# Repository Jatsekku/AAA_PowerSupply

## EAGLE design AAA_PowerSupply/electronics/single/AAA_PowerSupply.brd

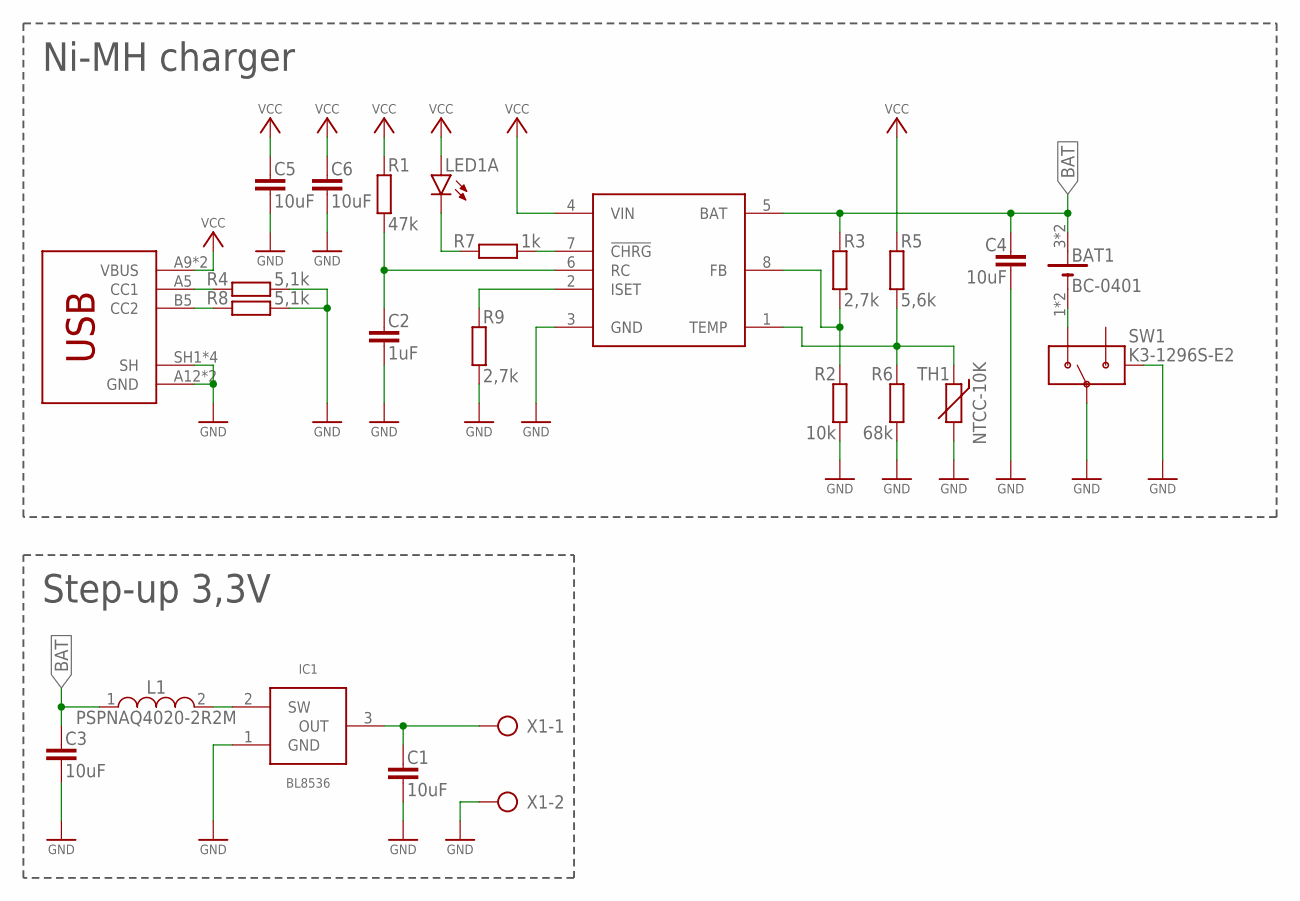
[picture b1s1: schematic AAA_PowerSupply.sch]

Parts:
BAT1: BC-0401
C1, C3, C4, C5, C6: 10uF; C0805
C2: 1uF; C0805
IC1: BL8536; SOT23
IC2: CN3085; SOP8_THERMAL
L1: PSPNAQ4020-2R2M; L-4X4
LED1: LSG-T676; WL-SFCW-0603
R1: 47k; R0805
R2: 10k; R0805
R3, R9: 2,7k; R0805
R4, R8: 5,1k; R0805
R5: 5,6k; R0805
R6: 68k; R0805
R7: 1k; R0805
SW1: K3-1296S-E2
TH1: NTCC-10K; RS-2,5
X1: AK500/2
X2: HC-TYPE-C-6P-01QT

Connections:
BAT: BAT1.3 (+), BAT1.4 (+), C3.1, C4.1, IC2.5 (BAT), L1.1, R3.1
GND: C1.2, C2.2, C3.2, C4.2, C5.2, C6.2, IC1.1 (GND), IC2.3 (GND), R2.2, R4.2, R6.2, R8.2, R9.1, SW1.P, SW1.SH1 (SH), SW1.SH2 (SH), SW1.SH3 (SH), SW1.SH4 (SH), TH1.2, X1.2, X2.A12 (GND), X2.B12 (GND), X2.SH1 (SH), X2.SH2 (SH), X2.SH3 (SH), X2.SH4 (SH)
unnamed: IC2.7 (!CHRG), R7.2
unnamed: LED1.P$1 (C), R7.1
unnamed: C2.1, IC2.6 (RC), R1.2
unnamed: IC2.2 (ISET), R9.2
unnamed: C1.1, IC1.3 (OUT), X1.1
unnamed: IC1.2 (SW), L1.2
unnamed: IC2.8 (FB), R2.1, R3.2
unnamed: IC2.1 (TEMP), R5.2, R6.1, TH1.1
unnamed: BAT1.1 (-), BAT1.2 (-), SW1.O
unnamed: R4.1, X2.A5 (CC1)
unnamed: R8.1, X2.B5 (CC2)
VCC: C5.1, C6.1, IC2.4 (VIN), LED1.P$2 (A), R1.1, R5.1, X2.A9 (VBUS), X2.B9 (VBUS)

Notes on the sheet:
Ni-MH charger
Step-up 3,3V

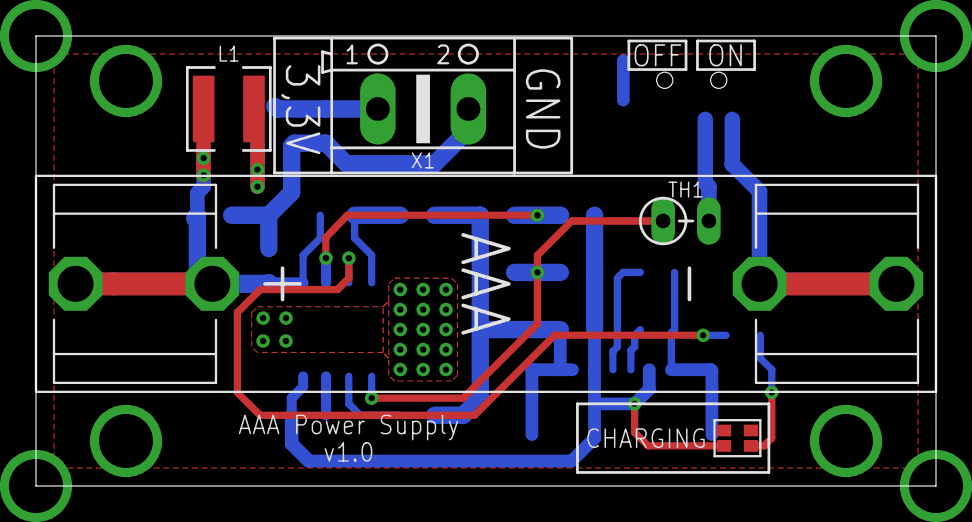
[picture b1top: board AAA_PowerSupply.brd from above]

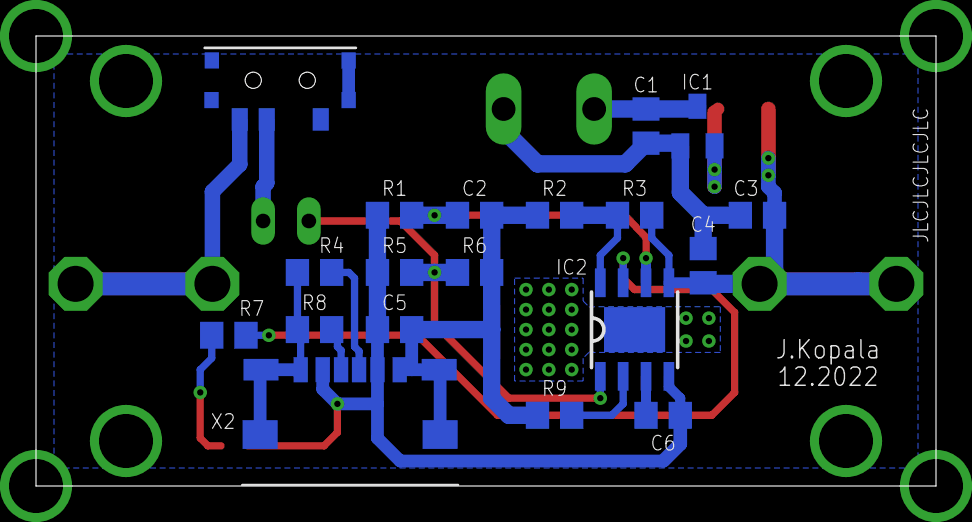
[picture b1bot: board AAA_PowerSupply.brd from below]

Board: 2 copper layers, 50.0 x 25.0 mm, 24 parts (19 on the bottom side), 14 nets.

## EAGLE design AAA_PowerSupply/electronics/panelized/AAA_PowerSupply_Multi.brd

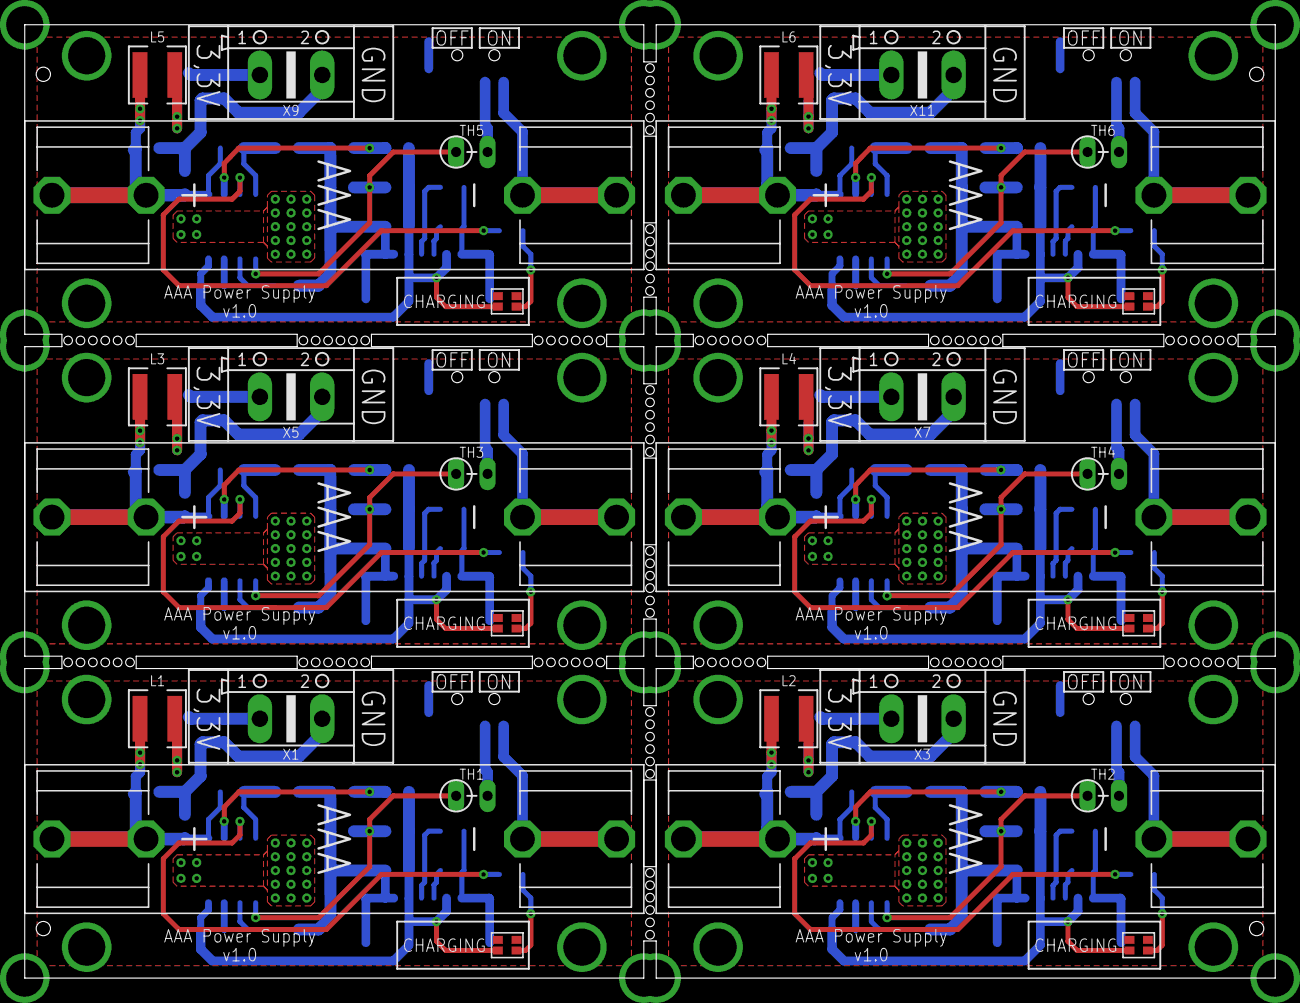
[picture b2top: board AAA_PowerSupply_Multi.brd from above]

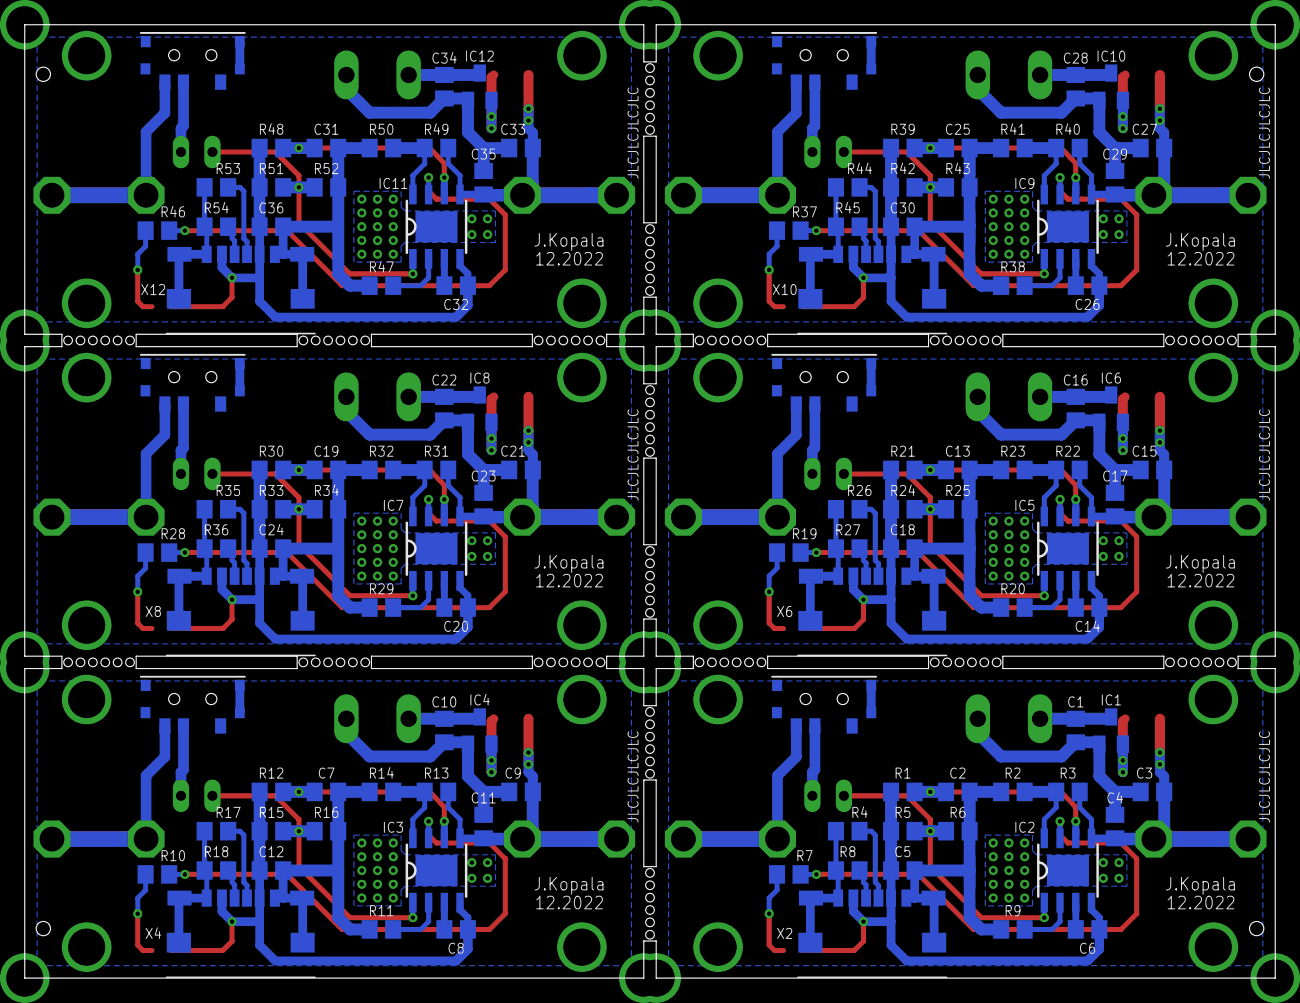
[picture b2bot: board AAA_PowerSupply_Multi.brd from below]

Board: 2 copper layers, 101.0 x 77.0 mm, 144 parts (114 on the bottom side), 84 nets.

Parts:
BAT1, BAT2, BAT3, BAT4, BAT5, BAT6: BC-0401
C1, C3, C4, C5, C6, C8, C9, C10, C11, C12, C14, C15, C16, C17, C18, C20, C21, C22, C23, C24, C26, C27, C28, C29, C30, C32, C33, C34, C35, C36: 10uF; C0805
C2, C7, C13, C19, C25, C31: 1uF; C0805
IC1, IC4, IC6, IC8, IC10, IC12: BL8536; SOT23
IC2, IC3, IC5, IC7, IC9, IC11: CN3085; SOP8_THERMAL
L1, L2, L3, L4, L5, L6: PSPNAQ4020-2R2M; L-4X4
LED1, LED2, LED3, LED4, LED5, LED6: LSG-T676; WL-SFCW-0603
R1, R12, R21, R30, R39, R48: 47k; R0805
R2, R14, R23, R32, R41, R50: 10k; R0805
R3, R9, R11, R13, R20, R22, R29, R31, R38, R40, R47, R49: 2,7k; R0805
R4, R8, R17, R18, R26, R27, R35, R36, R44, R45, R53, R54: 5,1k; R0805
R5, R15, R24, R33, R42, R51: 5,6k; R0805
R6, R16, R25, R34, R43, R52: 68k; R0805
R7, R10, R19, R28, R37, R46: 1k; R0805
SW1, SW2, SW3, SW4, SW5, SW6: K3-1296S-E2
TH1, TH2, TH3, TH4, TH5, TH6: NTCC-10K; RS-2,5
X1, X3, X5, X7, X9, X11: AK500/2
X2, X4, X6, X8, X10, X12: HC-TYPE-C-6P-01QT

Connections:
BAT: BAT1.3, BAT1.4, C3.1, C4.1, IC2.5, L1.1, R3.1
BAT1: BAT2.3, BAT2.4, C9.1, C11.1, IC3.5, L2.1, R13.1
BAT2: BAT3.3, BAT3.4, C15.1, C17.1, IC5.5, L3.1, R22.1
BAT3: BAT4.3, BAT4.4, C21.1, C23.1, IC7.5, L4.1, R31.1
BAT4: BAT5.3, BAT5.4, C27.1, C29.1, IC9.5, L5.1, R40.1
BAT5: BAT6.3, BAT6.4, C33.1, C35.1, IC11.5, L6.1, R49.1
GND: C1.2, C2.2, C3.2, C4.2, C5.2, C6.2, IC1.1, IC2.3, R2.2, R4.2, R6.2, R8.2, R9.1, SW1.P, SW1.SH1, SW1.SH2, SW1.SH3, SW1.SH4, TH1.2, X1.2, X2.A12, X2.B12, X2.SH1, X2.SH2, X2.SH3, X2.SH4
GND1: C7.2, C8.2, C9.2, C10.2, C11.2, C12.2, IC3.3, IC4.1, R11.1, R14.2, R16.2, R17.2, R18.2, SW2.P, SW2.SH1, SW2.SH2, SW2.SH3, SW2.SH4, TH2.2, X3.2, X4.A12, X4.B12, X4.SH1, X4.SH2, X4.SH3, X4.SH4
GND2: C13.2, C14.2, C15.2, C16.2, C17.2, C18.2, IC5.3, IC6.1, R20.1, R23.2, R25.2, R26.2, R27.2, SW3.P, SW3.SH1, SW3.SH2, SW3.SH3, SW3.SH4, TH3.2, X5.2, X6.A12, X6.B12, X6.SH1, X6.SH2, X6.SH3, X6.SH4
GND3: C19.2, C20.2, C21.2, C22.2, C23.2, C24.2, IC7.3, IC8.1, R29.1, R32.2, R34.2, R35.2, R36.2, SW4.P, SW4.SH1, SW4.SH2, SW4.SH3, SW4.SH4, TH4.2, X7.2, X8.A12, X8.B12, X8.SH1, X8.SH2, X8.SH3, X8.SH4
GND4: C25.2, C26.2, C27.2, C28.2, C29.2, C30.2, IC9.3, IC10.1, R38.1, R41.2, R43.2, R44.2, R45.2, SW5.P, SW5.SH1, SW5.SH2, SW5.SH3, SW5.SH4, TH5.2, X9.2, X10.A12, X10.B12, X10.SH1, X10.SH2, X10.SH3, X10.SH4
GND5: C31.2, C32.2, C33.2, C34.2, C35.2, C36.2, IC11.3, IC12.1, R47.1, R50.2, R52.2, R53.2, R54.2, SW6.P, SW6.SH1, SW6.SH2, SW6.SH3, SW6.SH4, TH6.2, X11.2, X12.A12, X12.B12, X12.SH1, X12.SH2, X12.SH3, X12.SH4
unnamed: C7.1, IC3.6, R12.2
unnamed: IC2.7, R7.2
unnamed: LED1.P$1, R7.1
unnamed: C2.1, IC2.6, R1.2
unnamed: IC2.2, R9.2
unnamed: C1.1, IC1.3, X1.1
unnamed: IC3.2, R11.2
unnamed: IC1.2, L1.2
unnamed: IC2.8, R2.1, R3.2
unnamed: C10.1, IC4.3, X3.1
unnamed: IC4.2, L2.2
unnamed: IC2.1, R5.2, R6.1, TH1.1
unnamed: IC3.8, R13.2, R14.1
unnamed: IC3.1, R15.2, R16.1, TH2.1
unnamed: IC3.7, R10.2
unnamed: LED2.P$1, R10.1
unnamed: BAT1.1, BAT1.2, SW1.O
unnamed: R4.1, X2.A5
unnamed: R8.1, X2.B5
unnamed: BAT2.1, BAT2.2, SW2.O
unnamed: R17.1, X4.A5
unnamed: R18.1, X4.B5
unnamed: C13.1, IC5.6, R21.2
unnamed: IC5.2, R20.2
unnamed: C16.1, IC6.3, X5.1
unnamed: IC6.2, L3.2
unnamed: IC5.8, R22.2, R23.1
unnamed: IC5.1, R24.2, R25.1, TH3.1
unnamed: IC5.7, R19.2
unnamed: LED3.P$1, R19.1
unnamed: BAT3.1, BAT3.2, SW3.O
unnamed: R26.1, X6.A5
unnamed: R27.1, X6.B5
unnamed: C19.1, IC7.6, R30.2
unnamed: IC7.2, R29.2
unnamed: C22.1, IC8.3, X7.1
unnamed: IC8.2, L4.2
unnamed: IC7.8, R31.2, R32.1
unnamed: IC7.1, R33.2, R34.1, TH4.1
unnamed: IC7.7, R28.2
unnamed: LED4.P$1, R28.1
unnamed: BAT4.1, BAT4.2, SW4.O
unnamed: R35.1, X8.A5
unnamed: R36.1, X8.B5
unnamed: C25.1, IC9.6, R39.2
unnamed: IC9.2, R38.2
unnamed: C28.1, IC10.3, X9.1
unnamed: IC10.2, L5.2
unnamed: IC9.8, R40.2, R41.1
unnamed: IC9.1, R42.2, R43.1, TH5.1
unnamed: IC9.7, R37.2
unnamed: LED5.P$1, R37.1
unnamed: BAT5.1, BAT5.2, SW5.O
unnamed: R44.1, X10.A5
unnamed: R45.1, X10.B5
unnamed: C31.1, IC11.6, R48.2
unnamed: IC11.2, R47.2
unnamed: C34.1, IC12.3, X11.1
unnamed: IC12.2, L6.2
unnamed: IC11.8, R49.2, R50.1
unnamed: IC11.1, R51.2, R52.1, TH6.1
unnamed: IC11.7, R46.2
unnamed: LED6.P$1, R46.1
unnamed: BAT6.1, BAT6.2, SW6.O
unnamed: R53.1, X12.A5
unnamed: R54.1, X12.B5
VCC: C5.1, C6.1, IC2.4, LED1.P$2, R1.1, R5.1, X2.A9, X2.B9
VCC1: C8.1, C12.1, IC3.4, LED2.P$2, R12.1, R15.1, X4.A9, X4.B9
VCC2: C14.1, C18.1, IC5.4, LED3.P$2, R21.1, R24.1, X6.A9, X6.B9
VCC3: C20.1, C24.1, IC7.4, LED4.P$2, R30.1, R33.1, X8.A9, X8.B9
VCC4: C26.1, C30.1, IC9.4, LED5.P$2, R39.1, R42.1, X10.A9, X10.B9
VCC5: C32.1, C36.1, IC11.4, LED6.P$2, R48.1, R51.1, X12.A9, X12.B9

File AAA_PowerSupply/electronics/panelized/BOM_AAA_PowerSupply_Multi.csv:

Comment,Designator ,Footprint,LCSC Part#
1k,"R7, R10, R19, R28, R37, R46",0805,C17513
"2,7k","R3, R9, R11, R13, R20, R22, R29, R31, R38, R40, R47, R49",0805,C17530
"5,1k","R4, R8, R17, R18, R26, R27, R35, R36, R44, R45, R53, R54",0805,C27834
"5,6k","R5, R15, R24, R33, R42, R51",0805,C4382
10k,"R2, R14, R23, R32, R41, R50",0805,C17414
47k,"R1, R12, R21, R30, R39, R48",0805,C17713
68k,"R6, R16, R25, R34, R43, R52",0805,C17801
1uF,"C2, C7, C13, C19, C25, C31",0805,C28323
10uF,"C1, C3, C4, C5, C6, C8, C9, C10, C11, C12, C14, C15, C16, C17, C18, C20, C21, C22, C23, C24, C26, C27, C28, C29, C30, C32, C33, C34, C35, C36",0805,C15850
BL8536,"IC1, IC4, IC6, IC8, IC10, IC12",SOT23-3,C97793
CN3085,"IC2, IC3, IC5, IC7, IC9, IC11",SOP8,C93054
HC-TYPE-C-6P-01QT,"X2, X4, X6, X8, X10, X12",HC-TYPE-C-6P-01QT,C2894895
K3-1296S-E2,"SW1, SW2, SW3, SW4, SW5, SW6",K3-1296S-E2,C136659
LSG-T676,"LED1, LED2, LED3, LED4, LED5, LED6, LED7, LED8",,

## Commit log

2023-01-12 electronics: Add complete design
    This commit contains all design files that were created as far:
    docs/ - contains datasheets of some parts used in project,
    panelized/ - production-ready files of panelized design,
    single/ - original single board design
